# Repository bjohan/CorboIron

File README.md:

# CorboIron

Soldering station with one pencil holder on bench.

Soldering station with both pencil holders hanging.

Side view

Front view

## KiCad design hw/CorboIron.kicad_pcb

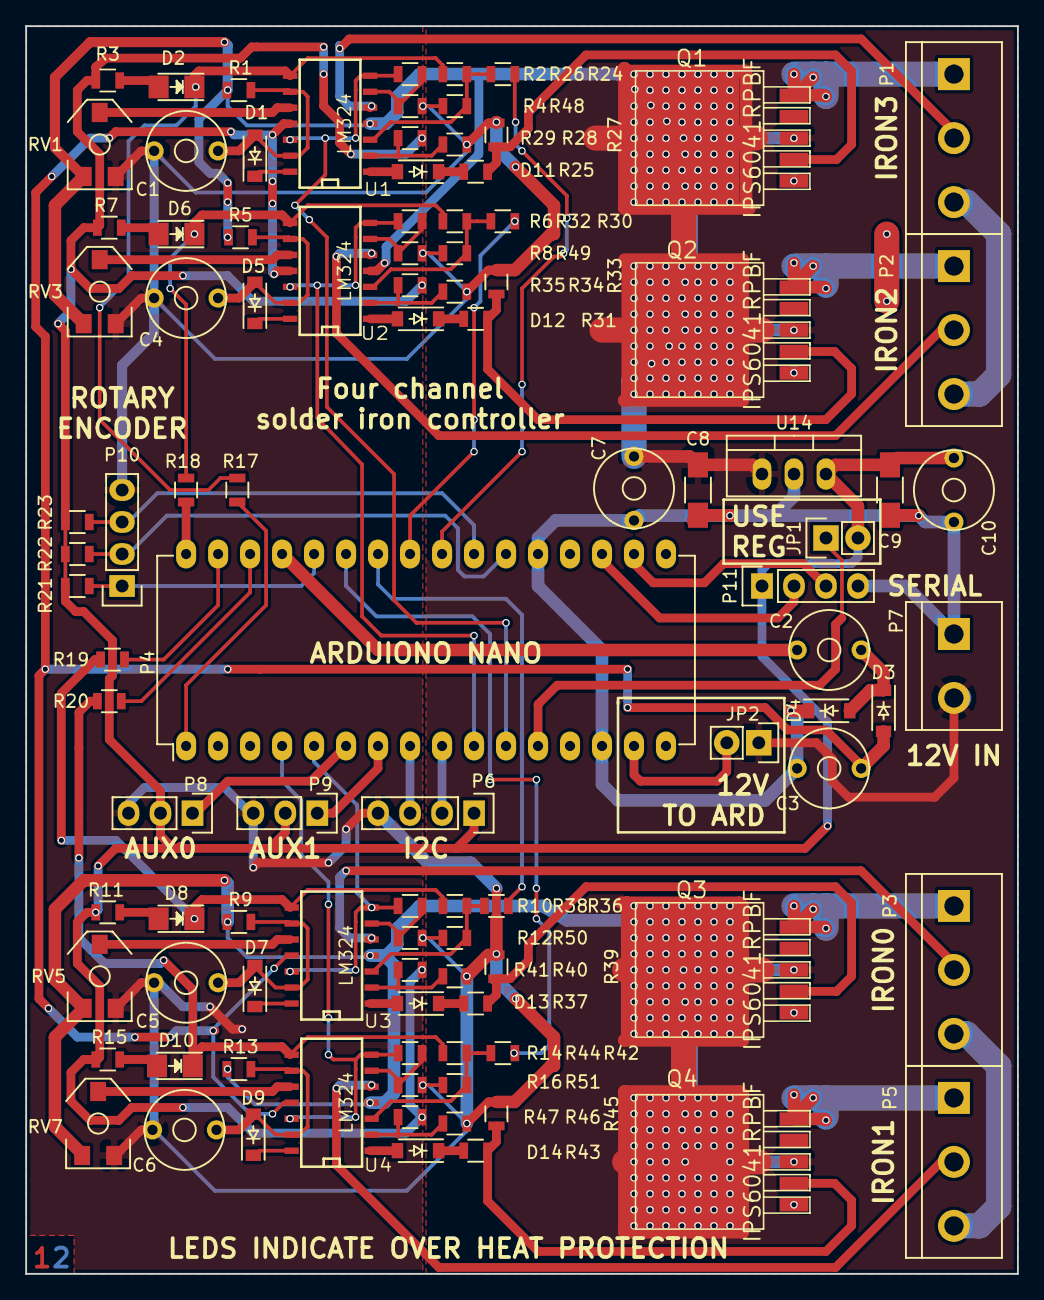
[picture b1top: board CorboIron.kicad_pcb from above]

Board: 2 copper layers, 78.7 x 99.1 mm, 101 parts (0 on the bottom side), 81 nets.

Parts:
C1, C4, C5, C6: 1uF; CV3-30PF
C2: 4u7; CV3-30PF
C3: 220u; CV3-30PF
C7, C10: 100u; CV3-30PF
C8, C9: 10n; C_1206_HandSoldering
D1, D3, D4, D5, D7, D9, D11, D12, D13, D14: D; SOD-123
D2, D6, D8, D10: LED; LED_1206
JP1, JP2: Jumper_NO_Small; Pin_Header_Straight_1x02
P1, P2, P3, P5: CONN_01X03; bornier3
P4: Arduino_nano; DIP-32_W15.24mm_LongPads
P6, P10, P11: CONN_01X04; Pin_Header_Straight_1x04
P7: CONN_01X02; bornier2
P8, P9: CONN_01X03; Pin_Header_Straight_1x03
Q1, Q2, Q3, Q4: IPS6041RPBF; DPAK5
R1, R5, R9, R13, R17, R18, R19, R20, R21, R22, R23: 100K; R_0805
R2, R6, R10, R14: 680K; R_0805
R3, R28, R29: 4k7; R_0805
R4, R8, R12, R16: 1K; R_0805
R7, R11, R15, R34, R35, R40, R41, R46, R47: 4K7; R_0805
R24, R30, R36, R42: 22K; R_0805
R25, R31, R37, R43: 6K8; R_0805
R26, R32, R38, R44: 150K; R_0805
R27, R33, R39, R45: 2K7; R_0805
R48, R49, R50, R51: 27K; R_0805
RV1, RV3, RV5, RV7: 5K; POT_SMD
U1, U2, U3, U4: LM324; SO14N
U14: 7805; TO-220_Neutral123_Vertical

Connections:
+5V: C9.1, C10.1, JP1.2, P6.1, P8.2, P9.2, P11.1, R3.1, R7.1, R11.1, R15.1, R21.1, R22.1, R23.1, R29.1, R35.1, R41.1, R47.1, U14.3
+12V: C7.1, C8.1, JP2.1, P7.2, Q1.3, Q2.3, Q3.3, Q4.3, R1.2, R5.2, R9.2, R13.2, RV1.1, RV3.1, RV5.1, RV7.1, U1.4, U2.4, U3.4, U4.4, U14.1
/5V_ARD: JP1.1, P4.12
/AUX0: P4.6, P8.1
/AUX1: P4.7, P9.1
/CHARGE_PUMP: C2.1, P4.29
/HTR0_CTL': D14.2, U4.1
/HTR0_EN: P4.27, R42.2
/HTR1_CTL: D13.2, U3.1
/HTR1_EN: P4.26, R36.2
/HTR2_CTL: D12.2, U2.1
/HTR2_EN: P4.25, R30.2
/HTR3_CTL: D11.2, U1.1
/HTR3_EN: P4.24, R24.2
/PUSH_SW: P4.28, P10.1, R21.2
/ROT_A: P4.22, P10.2, R22.2
/ROT_B: P4.23, P10.3, R23.2
/RX0: P4.19, P11.2
/SCL: P4.9, P6.2
/SDA: P4.8, P6.3
/TEMP0: P5.2, U4.5
/TEMP0_AMP: P4.4, R14.2, U4.7, U4.12
/TEMP0_MIN: C6.1, D9.2, R13.1, U4.9, U4.13
/TEMP0_OK: D10.1, R20.2, R44.2, U4.8
/TEMP1: P3.2, U3.5
/TEMP1_AMP: P4.5, R10.2, U3.7, U3.12
/TEMP1_MIN: C5.1, D7.2, R9.1, U3.9, U3.13
/TEMP1_OK: D8.1, R19.2, R38.2, U3.8
/TEMP2: P2.2, U2.5
/TEMP2_AMP: P4.10, R6.2, U2.7, U2.12
/TEMP2_MIN: C4.1, D5.2, R5.1, U2.9, U2.13
/TEMP2_OK: D6.1, R18.2, R32.2, U2.8
/TEMP3: P1.2, U1.5
/TEMP3_AMP: P4.11, R2.2, U1.7, U1.12
/TEMP3_MIN: C1.1, D1.2, R1.1, U1.9, U1.13
/TEMP3_OK: D2.1, R17.2, R26.2, U1.8
/TX1: P4.18, P11.3
/VIN: JP2.2, P4.15
/V_NEG: C3.2, D3.2, U1.11, U2.11, U3.11, U4.11
GND: C1.2, C3.1, C4.2, C5.2, C6.2, C7.2, C8.2, C9.2, C10.2, D4.1, P1.3, P2.3, P3.3, P4.14, P4.21, P5.3, P6.4, P7.1, P8.3, P9.3, P10.4, P11.4, Q1.1, Q2.1, Q2.4, Q3.1, Q4.1, R4.1, R8.1, R12.1, R16.1, R27.1, R28.2, R33.1, R34.2, R39.1, R40.2, R45.1, R46.2, R48.1, R49.1, R50.1, R51.1, RV1.3, RV3.3, RV5.3, RV7.3, U14.2
unnamed: C2.2, D3.1, D4.2
unnamed: D1.1, U1.14
unnamed: D2.2, R3.2
unnamed: D5.1, U2.14
unnamed: D6.2, R7.2
unnamed: D7.1, U3.14
unnamed: D8.2, R11.2
unnamed: D9.1, U4.14
unnamed: D10.2, R15.2
unnamed: D11.1, R25.2
unnamed: D12.1, R31.2
unnamed: D13.1, R37.2
unnamed: D14.1, R43.2
unnamed: P1.1, Q1.5
unnamed: P2.1, Q2.5
unnamed: P3.1, Q3.5
unnamed: P4.1, R17.1
unnamed: P4.30, R20.1
unnamed: P4.31, R19.1
unnamed: P4.32, R18.1
unnamed: P5.1, Q4.5
unnamed: Q1.2, R25.1, R27.2
unnamed: Q2.2, R31.1, R33.2
unnamed: Q3.2, R37.1, R39.2
unnamed: Q4.2, R43.1, R45.2
unnamed: R2.1, R4.2, U1.6
unnamed: R6.1, R8.2, U2.6
unnamed: R10.1, R12.2, U3.6
unnamed: R14.1, R16.2, U4.6
unnamed: R24.1, R26.1, R48.2, U1.3
unnamed: R28.1, R29.2, U1.2
unnamed: R30.1, R32.1, R49.2, U2.3
unnamed: R34.1, R35.2, U2.2
unnamed: R36.1, R38.1, R50.2, U3.3
unnamed: R40.1, R41.2, U3.2
unnamed: R42.1, R44.1, R51.2, U4.3
unnamed: R46.1, R47.2, U4.2
unnamed: RV1.2, U1.10
unnamed: RV3.2, U2.10
unnamed: RV5.2, U3.10
unnamed: RV7.2, U4.10

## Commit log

2016-03-20 Reorganized arduinofiles and added working version och schematic
2016-03-20 Started PCB
2016-03-20 Tried to add footprints
2016-03-20 Started placing componets
2016-03-24 Horror!
2016-03-24 Started pretty version
2016-03-25 Completely routed but not pretty or functional, need wider traces for the heater currents!
2016-03-25 Some via stitching
2016-03-25 perhaps usable
2016-03-26 Added gerber and drl files
2016-03-26 Added box
2016-03-27 Added pulldown resistors for opamp logic started placeing refdes and values on silkscreen
2016-03-27 Tidying up of silkscreen
2016-03-27 Added plots
2016-03-28 Added descriptive text in silk
2016-03-29 Minor changes
2016-04-18 Checked footprints, design should be ready for production
2016-04-19 Added files sent to production
2016-05-06 Started adaptations for new board
2016-05-15 Started adding 3d party libs
2016-06-02 Started work on standing box, metcal-ish
2016-06-06 More work on the standing box
2016-06-26 Added solder iron stand
2016-07-14 dont remember exactly :)
2016-07-14 More work on display
2016-07-14 More LCD-stuff
2016-07-16 Started work on regulator
2016-07-17 Some coarse P regulation for each channel
2016-09-24 Made box out of separate panels to simplify printing
2016-10-01 Started working on the pen
2017-07-21 Temperature is somewhat sane, about 5 C error between 150 and 350 C but the ADC used seems to be not perfect so this probably only works for this individual hardware
2017-07-23 Untested code , but started moving sampling and pwm to an interrupt
2017-07-26 Semi functional mess
2018-01-10 Reverted schematic
2018-01-27 Reference point if i decide to go back from more fixed point instead of floating point
2018-08-14 Happy hacking, really neads cleaning
2018-08-16 Minor adjustments
